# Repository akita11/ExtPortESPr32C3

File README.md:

# ExtPort For ESPr32-C3

[スイッチサイエンス社のESPr® Developer C3](https://www.switch-science.com/products/9185)に接続して最大4つのGroveコネクタを増設し、複数のGrove接続のUNIT等を接続することができます。

ESPr® Developer C3は上図の向きに接続してください。
（ESPr® Developer C3にヘッダピンを取り付けていない場合は、はんだ付けしてください）

## Groveコネクタのピン配置

4つのGroveコネクタのピン配置は以下のとおりです。
VDD（電源+5V）はESPr® Developer C3から供給されます。

- PortA（赤）: IO2/IO3/VDD/GND
- PortB（黒）: IO4/IO5/VDD/GND
- PortC（青）: IO20/IO21/VDD/GND
- PortD（緑）: IO8/IO9/VDD/GND

なおESPr® Developer C3の横の端子には、ESPr® Developer C3の各端子がそのまま接続されています。

## Author

Junichi Akita (@akita11) / akita@ifdl.jp

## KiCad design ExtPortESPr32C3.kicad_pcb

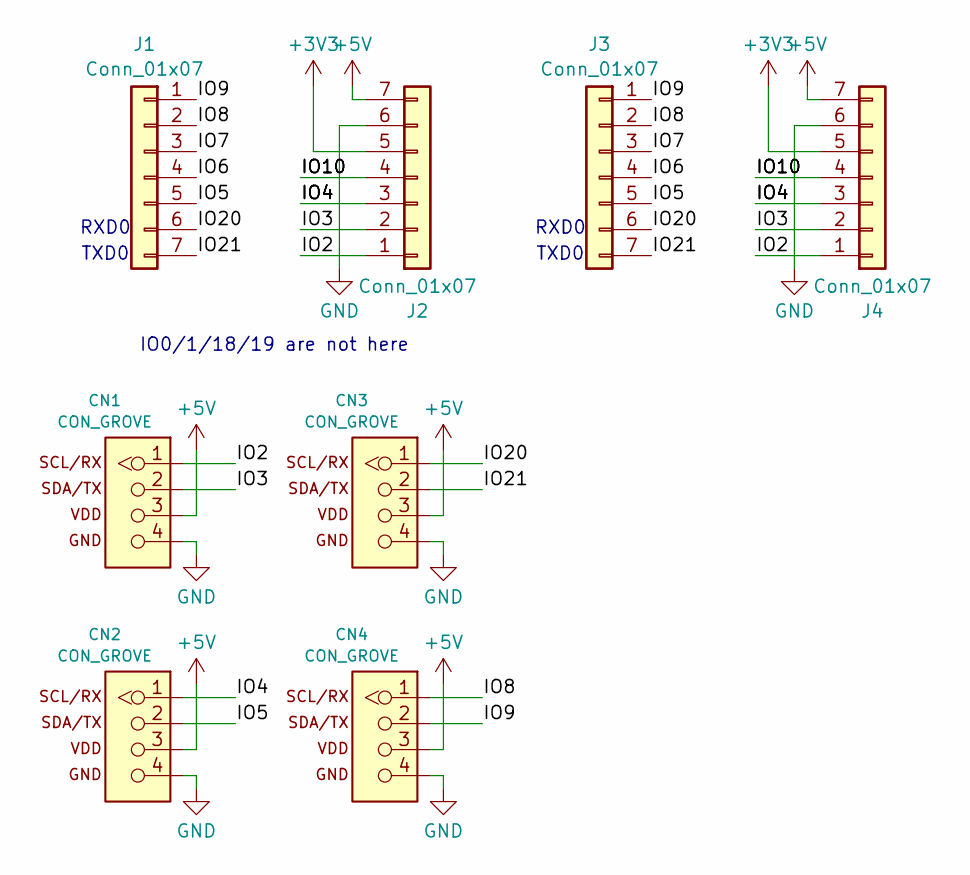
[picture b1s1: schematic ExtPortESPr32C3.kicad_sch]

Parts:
CN1, CN2, CN3, CN4: CON_GROVE; CON_GROVE_V_roundPad
J1, J2, J3, J4: Conn_01x07; PinSocket_1x07_P2.54mm_Vertical

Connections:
+3V3: J2.5, J4.5
+5V: CN1.3, CN2.3, CN3.3, CN4.3, J2.7, J4.7
/IO2: CN1.1, J2.1, J4.1
/IO3: CN1.2, J2.2, J4.2
/IO4: CN2.1, J2.3, J4.3
/IO5: CN2.2, J1.5, J3.5
/IO6: J1.4, J3.4
/IO7: J1.3, J3.3
/IO8: CN4.1, J1.2, J3.2
/IO9: CN4.2, J1.1, J3.1
/IO10: J2.4, J4.4
/IO20: CN3.1, J1.6, J3.6
/IO21: CN3.2, J1.7, J3.7
GND: CN1.4, CN2.4, CN3.4, CN4.4, J2.6, J4.6

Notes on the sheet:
TXD0
RXD0
IO0/1/18/19 are not here

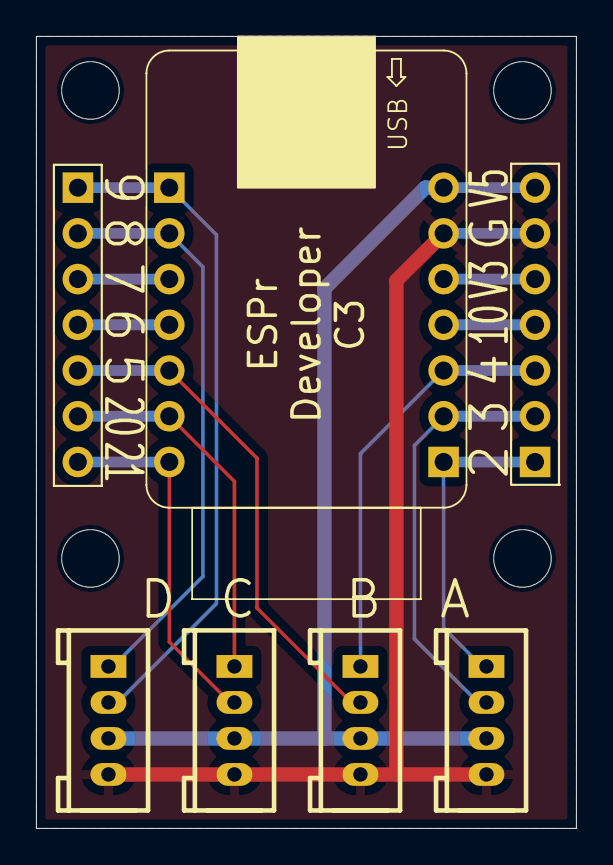
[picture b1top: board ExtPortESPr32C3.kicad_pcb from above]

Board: 2 copper layers, 30.0 x 44.0 mm, 8 parts (0 on the bottom side), 14 nets.

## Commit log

2026-03-07 initlal commit
2026-03-17 add photo
